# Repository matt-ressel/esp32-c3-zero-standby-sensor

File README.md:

# ESP32-C3 Zero-Standby Environmental Sensor

## 🎯 Project Goal

To create a wireless, battery-powered environmental sensor, optimized for extremely low power consumption. The primary goal is to achieve a theoretical battery life exceeding **10 years** on a single Li-SOCl₂ (e.g., FANSO ER18505M 3.6V, 3500mAh) battery.

This project achieves this goal through a unique **"Zero Standby"** architecture, where the microcontroller is completely disconnected from power during its idle state. The duty cycle is managed by an external, nano-power system timer.

---

## 🚀 Key Features & Architecture

*   **Ultra-Low Electronic Quiescent Current:** The total current consumed by the electronics in the power-off state has been meticulously optimized to be under 100 nA. This value is the sum of the quiescent currents (Iq) of all components permanently connected to the battery:
    *   **TPS63900 Buck-Boost (in shutdown):** ~60 nA
    *   **TPL5111 System Timer:** ~35 nA
    *   **SiP32431 Load Switch (in off-state):** ~0.01 nA (practically zero)
    *   **Total Electronic Iq ≈ 95 nA**

    This successfully achieves the design goal of making the electronic footprint in the standby state almost immeasurable. It ensures that the theoretical battery life is maximized, being limited almost exclusively by the energy consumed during the brief active cycles.
*   **Power Gating Architecture:** Instead of using Deep Sleep mode, the TPL5111 completely enables and disables the power supply for the entire system (MCU + sensor), eliminating any MCU-related leakage currents.
*   **Ultra-Fast On-Time:** The entire active cycle (boot, measure, transmit, shutdown) is highly optimized to complete in **well under 100 milliseconds** (typically ~80ms), which is critical for minimizing energy consumption.
*   **Optimized Operational Sequence:** The firmware uses advanced techniques like **latency hiding**, where long physical processes (like battery measurement stabilization) are executed in the background during other necessary initializations (like the Wi-Fi stack), effectively reducing their time cost to zero.
*   **ESP-NOW Communication:** Utilizes the lightweight and fast ESP-NOW protocol, configured for Long Range (LR) mode, for robust and low-power data transmission.
*   **Professional Component-Based Architecture:** The code is structured into fully independent, reusable components (e.g., `bme280_driver`, `espnow_sender`, `sensor_manager`) in line with the best practices for ESP-IDF, ensuring clean separation of concerns and easy maintenance.

---

## 🛠️ Hardware Components (Bill of Materials)

| Component             | Model/Value                                     | Role                                                     |
| --------------------- | ----------------------------------------------- | -------------------------------------------------------- |
| **Microcontroller**   | Espressif ESP32-C3-MINI-1                       | Main processing unit, RF communication                   |
| **System Timer**        | Texas Instruments TPL5111                       | External watchdog and duty cycle manager (Power Gating)  |
| **Buck-Boost Converter**| Texas Instruments TPS63900                      | High-efficiency 3.3V voltage regulation                |
| **Environmental Sensor**| Bosch BME280                                    | Measures temperature, humidity, and pressure (I²C)       |
| **Battery**             | FANSO ER18505M (Li-SOCl₂, 3.6V, 3500mAh) or similar | Primary power source                                     |
| **Load Switch**         | Vishay SiP32431                                 | Switched voltage divider for V_BATT measurement        |

---

## 🔄 Optimized Software Operational Sequence

The duty cycle is fast, repeatable, and designed for maximum efficiency. The order of operations is critical.

1.  **START (Cold Boot):** The TPL5111 activates the power converter, supplying power to the system. `app_main` begins execution.

2.  **IMMEDIATE CRITICAL ACTIONS:**
    *   **Initialize Critical Drivers:** The bare minimum of drivers needed for immediate measurements are initialized (`bme280_driver`, `battery_monitor`, `power_manager`).
    *   **Start Battery Measurement:** The firmware immediately enables the external voltage divider. This starts the ~25ms physical process of charging the filter capacitor. This process now runs **in the background**.
    *   **Perform BME280 Measurement:** With the battery measurement stabilizing in the background, the CPU **immediately** performs the BME280 sensor reading. This is done as early as possible to get a temperature reading before the CPU core begins to self-heat.

3.  **LATENCY HIDING & NETWORK INIT:**
    *   While the battery measurement capacitor is charging, the firmware productively uses this time to initialize the time-consuming network stack (`wifi_service` and `espnow_sender`). This **hides the 25ms delay**, effectively making the battery stabilization time "free".

4.  **FINALIZE & TRANSMIT:**
    *   Control is passed to the `sensor_manager`.
    *   It **finalizes the battery measurement** by reading the now-stable voltage from the ADC.
    *   It assembles all data (BME280, battery) into a payload, calculates a CRC, and hands it to the `espnow_sender`.
    *   The `espnow_sender` transmits the packet and waits for a hardware-level acknowledgement (ACK) from the receiver.

5.  **SHUTDOWN:**
    *   Upon completion of the transmission (successful or not), a HIGH pulse is generated on the `DONE` pin.
    *   The TPL5111 receives the signal and immediately cuts off power to the system.
    *   A **fail-safe mechanism** is in place: if the shutdown signal fails, the MCU enters its deepest possible sleep state to conserve energy until the TPL5111's own watchdog timer performs a hard power cycle.

---

## ⚙️ Getting Started & Configuration

This project is designed for rapid setup using the provided configuration files, while still requiring user-specific network details.

### 1. Mandatory User Configuration (menuconfig)

This repository includes a pre-configured `sdkconfig` file containing all the performance optimizations listed below. This saves you the time of setting them manually.

**However, you MUST configure your own network-specific parameters before building and flashing.**

To do this, run `idf.py menuconfig` and navigate to the following menu:

`---> ESP32C3 Zero Standby Sensor Configuration`

Inside this menu, you must set the following values to match your receiver/gateway:

*   **`Gateway MAC Address`**: The MAC address of your ESP-NOW receiver.
*   **`ESPNOW primary master key (PMK)`**: A 16-character string shared with the receiver.
*   **`ESPNOW local master key (LMK)`**: A 16-character string shared with the receiver for this specific device.
*   **`ESPNOW Channel`**: The Wi-Fi channel (1-13) on which both devices will communicate.
*   **`I2C Pin Configuration`**: Specify the GPIO pins used by the I2C master for the BME280.

### 2. Summary of Key Performance Optimizations

For reference, here is a detailed list of the critical optimizations applied in the provided `sdkconfig` to achieve an ultra-fast boot time (cold boot to shutdown in < 100ms).

The following options, configured via `idf.py menuconfig`, are essential for minimizing boot time and runtime power consumption.

#### Compiler Optimization
For maximum performance, both the main application and the bootloader should be compiled with `-O2` optimization.
*   **Application Optimization Level:**
    *   `Compiler options ---> Optimization Level ---> Optimize for performance (-O2)`

*   **Bootloader Optimization Level:**
    *   `Bootloader config ---> Bootloader optimization level ---> Optimize for performance (-O2)`

#### Bootloader & Logging & System
*   **Disable Console Output (CRITICAL):** Disables the UART console driver entirely. This removes the initialization overhead of the UART peripheral and converts all logging macros to no-ops, significantly speeding up boot and execution.
    *   `Component config ---> ESP System Settings ---> Channel for console output (None)`

*   **Skip Image Validation:** This is a major optimization. It instructs the bootloader to skip the time-consuming SHA-256 validation of the application image on every boot.
    *   `Bootloader config ---> [*] Skip image validation always`

*   **Disable Bootloader Log:** Drastically speeds up the initial boot phase.
    *   `Bootloader config ---> Log ---> Bootloader log verbosity ---> No output`

*   **Disable Application Log:** Frees up CPU cycles and reduces on-time. Set to "Info" for debugging and "None" for production.
    *   `Component config ---> Log ---> Log Level ---> Default log verbosity ---> No output`

*   **FreeRTOS:** The project is configured for a single core and a 1000Hz tick rate.
    *   `Component config ---> FreeRTOS ---> Kernel ---> configTICK_RATE_HZ (1000)`

#### ADC & RTC Optimizations
*   **Place ADC ISR in IRAM:** Improves performance of ADC reads by running the code from faster RAM instead of flash.
    *   `Component config ---> ADC ---> [*] Place ISR version ADC oneshot mode read function into IRAM`

*   **Skip RTC Clock Calibration:** Reduces boot time by skipping a time-consuming calibration step.
    *   `Component config ---> Hardware Settings ---> RTC Clock Config ---> (0) Number of cycles for RTC_SLOW_CLK calibration`    

#### Wi-Fi, PHY & LWIP Stack Reduction
The goal is to strip down the network stack to the bare minimum required for ESP-NOW.
*   **Reduce Max TX Power:** A critical setting to reduce peak current draw and stay within the limits of the power supply and battery. 18dBm is a safe starting point.
    *   `Component config ---> Wi-Fi ---> (18) Max WiFi TX power (dBm)`
    
*   **Enable Brownout Power Reduction:** A fail-safe mechanism that reduces Tx power on the next boot if a brownout occurs.
    *   `Component config ---> PHY ---> [*] Reduce PHY TX power when brownout reset`

*   **Disable Unused Wi-Fi Features:** ESP-NOW does not require SoftAP, WPA3, Enterprise security, or OWE. Disabling these significantly reduces the final binary size and memory footprint.
    *   `Component config ---> Wi-Fi ---> [ ] WiFi SoftAP Support`
    *   `Component config ---> Wi-Fi ---> Security features ---> [ ] Enable WPA3-Personal`
    *   And other similar options...

*   **Disable LWIP (TCP/IP Stack):** ESP-NOW operates at the MAC layer and does not use the TCP/IP stack (LWIP). Disabling IPv6 and DHCP server further reduces code size and memory usage.
    *   `Component config ---> LWIP ---> [ ] Enable IPv6`
    *   `Component config ---> LWIP ---> [ ] DHCPS: Enable IPv4 Dynamic Host Configuration Protocol Server (DHCPS)`

#### Flash & PHY
*   **SPI Flash Configuration:** Using the fastest possible mode and frequency reduces the time spent loading the application from flash.
    *   `Serial flasher config ---> Flash SPI mode ---> QIO`
    *   `Serial flasher config ---> Flash SPI speed ---> 80 MHz`
    
*   **Disable PHY Calibration:** Skips Wi-Fi/Bluetooth PHY calibration on boot, saving a significant amount of time. This is safe as calibration data is stored in NVS and loaded on first boot.
    *   `Component config ---> PHY ---> [*] Store phy calibration data in NVS`
    *   `Component config ---> PHY ---> Calibration mode (Calibration none)`
 
### 3. Boot ROM Log Disable (eFuse) - CRITICAL STEP

By default, the ESP32-C3's internal Boot ROM prints diagnostic messages to the UART during the very first moments of startup. This adds a significant delay. Disabling this is a **one-way, irreversible operation** that requires burning eFuses.

**Warning: Burning eFuses is permanent. Proceed with caution.**

To achieve the fastest possible boot time, connect the device and run the following commands using `espefuse.py`:

```bash
# Disable ROM logs for UART0
espefuse.py --port YOUR_PORT burn_efuse UART_PRINT_CONTROL 3

# For ESP32-C3 with built-in USB-JTAG, also disable its ROM logs
espefuse.py --port YOUR_PORT burn_efuse DIS_USB_SERIAL_JTAG_ROM_PRINT 1    

```

## 📉 Real-World Performance Verification

The theoretical optimizations have been verified using a **Nordic Power Profiler Kit II (PPK2)**. The chart below captures a single, complete active cycle — from cold boot, through sensor reading and Wi-Fi initialization, to ESP-NOW transmission and final power-off.

*(Fig. 1: Complete active cycle profile captured with PPK2 @ 3.6V)*

### Measured Metrics (per cycle):

| Metric | Measured Value | Significance |
| :--- | :--- | :--- |
| **Total On-Time** | **~80 ms** | Surpasses the goal of < 100ms. Minimizes the time the battery is under load. |
| **Total Charge** | **~3.05 mC** | Extremely low energy cost per transmission. **1 mC ≈ 0.278 µAh**, so one cycle costs just **~0.85 µAh**. |
| **Average Current** | **~38 mA** | Efficient operation during the active phase. |
| **Peak Current** | **~430 mA** | Represents the short Wi-Fi TX burst. Handled by input capacitors to protect the high-impedance battery. |

**Conclusion:** With a total charge of **3.05 mC** per cycle and a 10-minute interval, the average current consumption of the electronics is approximately **0.25 µA** (plus the ~200nA quiescent current). This confirms that the system's battery life is strictly limited by the battery's self-discharge rate, not the device's power consumption.

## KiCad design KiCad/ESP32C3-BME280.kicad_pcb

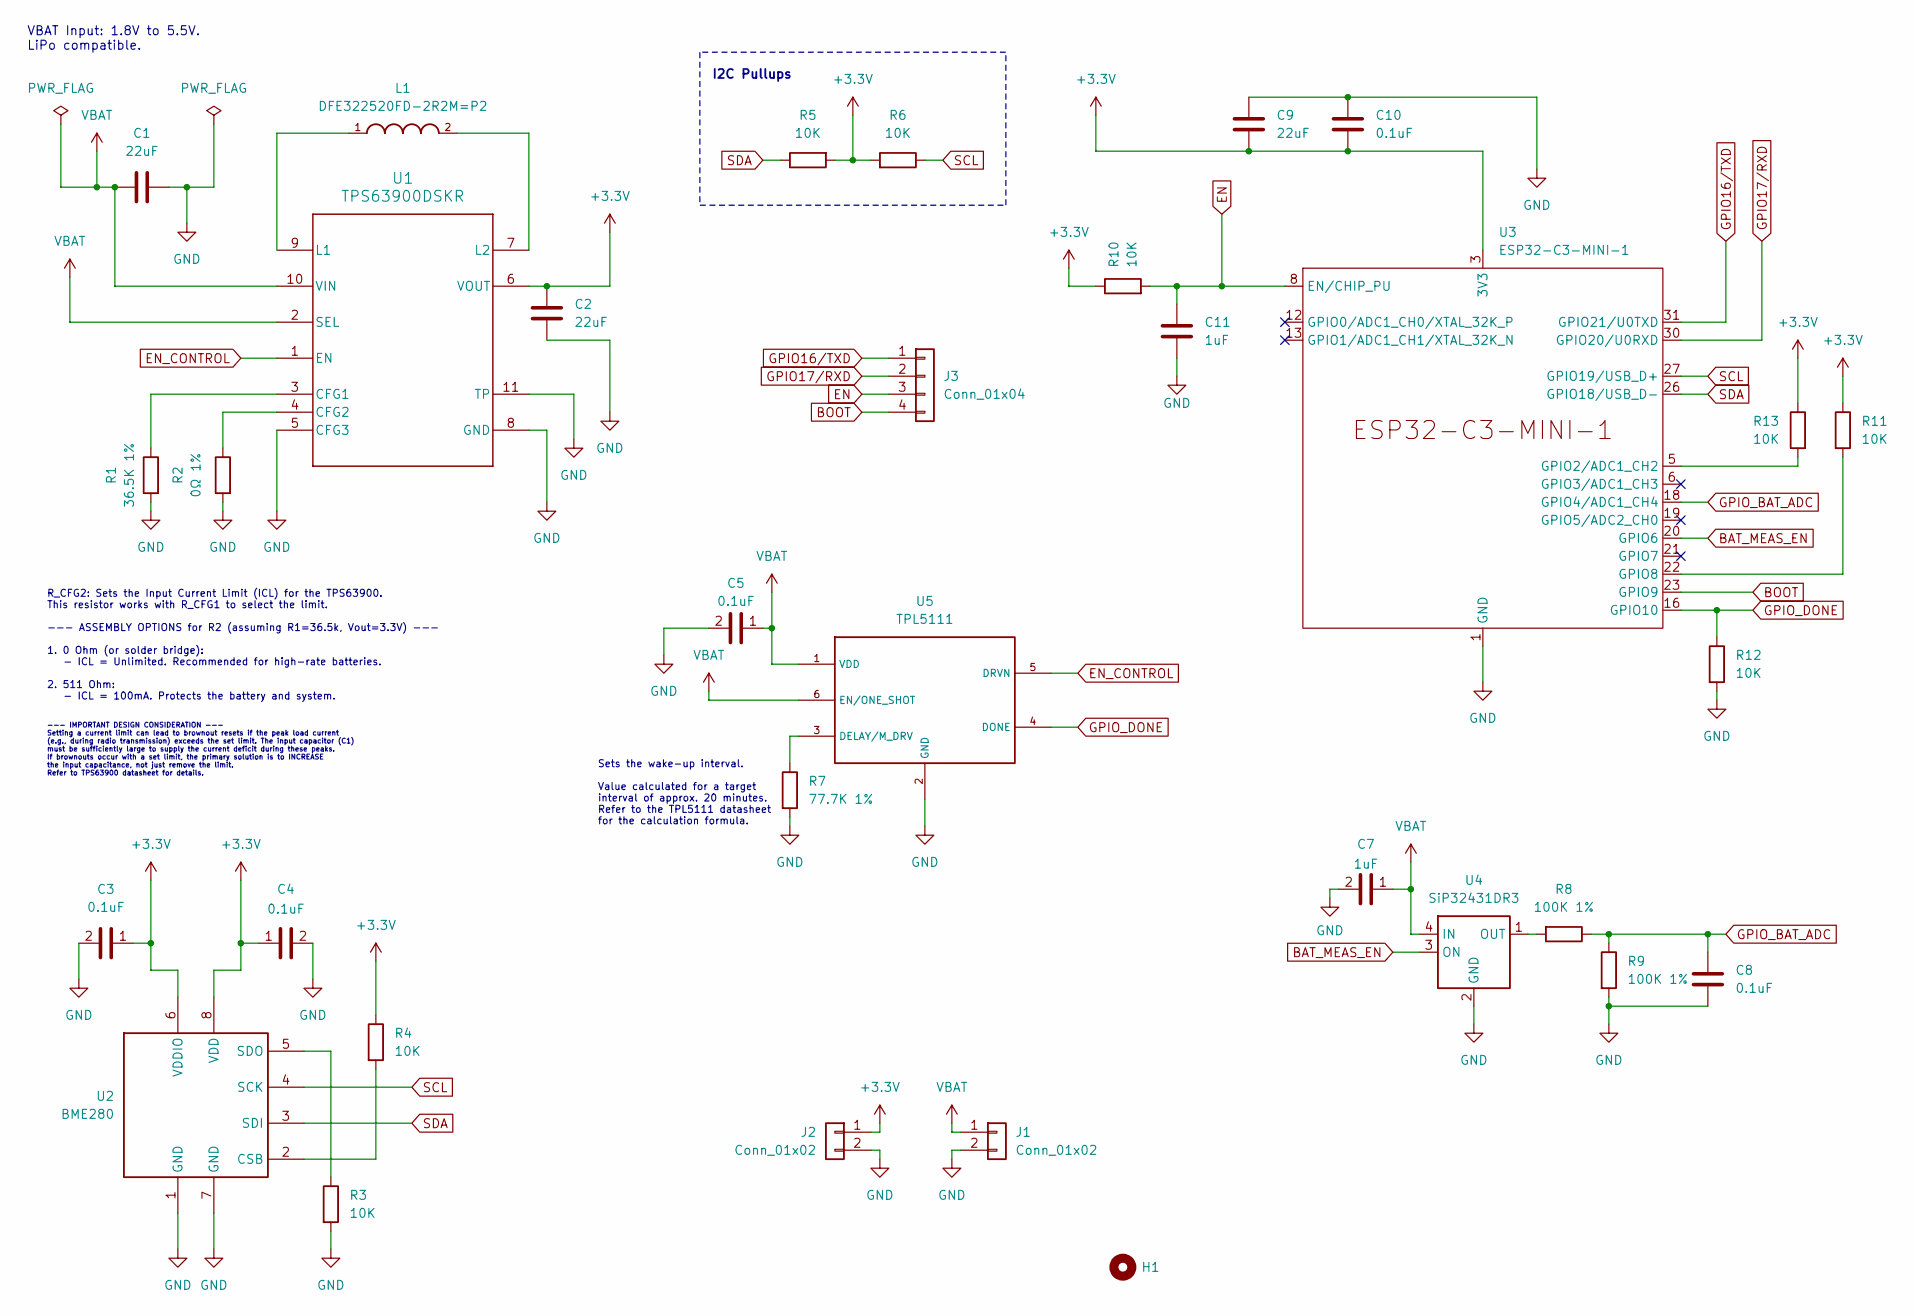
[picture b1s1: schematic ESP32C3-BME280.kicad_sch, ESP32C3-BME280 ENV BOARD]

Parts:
C1, C2, C9: 22uF; C_0805_2012Metric
C3, C4, C5, C8, C10: 0.1uF; C_0603_1608Metric
C7, C11: 1uF; C_0603_1608Metric
H1: MountingHole; MountingHole_2.2mm_M2_ISO7380_Pad
J1, J2: Conn_01x02; PinHeader_1x02_P2.00mm_Vertical
J3: Conn_01x04; PinHeader_1x04_P2.00mm_Vertical
L1: DFE322520FD-2R2M=P2; INDC3225X200N
R1: 36.5K 1%; R_0603_1608Metric
R2: 0Ω 1%; R_0603_1608Metric
R3, R4, R5, R6, R10, R11, R12, R13: 10K; R_0603_1608Metric
R7: 77.7K 1%; R_0603_1608Metric
R8, R9: 100K 1%; R_0603_1608Metric
U1: TPS63900DSKR; DSK0010A
U2: BME280; Bosch_LGA-8_2.5x2.5mm_P0.65mm_ClockwisePinNumbering
U3: ESP32-C3-MINI-1
U4: SiP32431DR3; SOT-363_SC-70-6
U5: TPL5111; SOT-23-6

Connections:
+3.3V: C2.1, C3.1, C4.1, C9.1, C10.1, J2.1, R4.1, R5.2, R6.2, R10.1, R11.1, R13.1, U1.6 (VOUT), U2.6 (VDDIO), U2.8 (VDD), U3.3 (3V3)
BAT_MEAS_EN: U3.20 (GPIO6), U4.3 (ON)
BOOT: J3.4, U3.23 (GPIO9)
EN: C11.1, J3.3, R10.2, U3.8 (EN/CHIP_PU)
EN_CONTROL: U1.1 (EN), U5.5 (DRVN)
GND: C1.2, C2.2, C3.2, C4.2, C5.2, C7.2, C8.2, C9.2, C10.2, C11.2, J1.2, J2.2, R1.2, R2.2, R3.2, R7.2, R9.2, R12.2, U1.5 (CFG3), U1.8 (GND), U1.11 (TP), U2.1 (GND), U2.7 (GND), U3.1 (GND), U3.2 (GND), U3.11 (GND), U3.14 (GND), U3.36 (GND), U3.37 (GND), U3.38 (GND), U3.39 (GND), U3.40 (GND), U3.41 (GND), U3.42 (GND), U3.43 (GND), U3.44 (GND), U3.45 (GND), U3.46 (GND), U3.47 (GND), U3.48 (GND), U3.49 (GND), U3.50 (GND), U3.51 (GND), U3.52 (GND), U3.53 (GND), U4.2 (GND), U4.5 (GND), U5.2 (GND)
GPIO16/TXD: J3.1, U3.31 (GPIO21/U0TXD)
GPIO17/RXD: J3.2, U3.30 (GPIO20/U0RXD)
GPIO_BAT_ADC: C8.1, R8.1, R9.1, U3.18 (GPIO4/ADC1_CH4)
GPIO_DONE: R12.1, U3.16 (GPIO10), U5.4 (DONE)
unnamed: R1.1, U1.3 (CFG1)
unnamed: R2.1, U1.4 (CFG2)
unnamed: L1.1, U1.9 (L1)
unnamed: L1.2, U1.7 (L2)
unnamed: R4.2, U2.2 (CSB)
unnamed: R3.1, U2.5 (SDO)
unnamed: R13.2, U3.5 (GPIO2/ADC1_CH2)
unnamed: R11.2, U3.22 (GPIO8)
unnamed: R8.2, U4.1 (OUT)
unnamed: R7.1, U5.3 (DELAY/M_DRV)
SCL: R6.1, U2.4 (SCK), U3.27 (GPIO19/USB_D+)
SDA: R5.1, U2.3 (SDI), U3.26 (GPIO18/USB_D-)
VBAT: C1.1, C5.1, C7.1, J1.1, U1.2 (SEL), U1.10 (VIN), U4.4 (IN), U5.1 (VDD), U5.6 (EN/ONE_SHOT)

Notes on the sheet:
Sets the wake-up interval. Value calculated for a target interval of approx. 20 minutes. Refer to the TPL5111 datasheet for the calculation formula.
R_CFG2: Sets the Input Current Limit (ICL) for the TPS63900. This resistor works with R_CFG1 to select the limit. --- ASSEMBLY OPTIONS for R2 (assuming R1=36.5k, Vout=3.3V) --- 1. 0 Ohm (or solder bridge): - ICL = Unlimited. Recommended for high-rate batteries. 2. 511 Ohm: - ICL = 100mA. Protects t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
I2C Pullups
--- IMPORTANT DESIGN CONSIDERATION --- Setting a current limit can lead to brownout resets if the peak load current (e.g., during radio transmission) exceeds the set limit. The input capacitor (C1) must be sufficiently large to supply the current deficit during these peaks. If brownouts occur with 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
VBAT Input: 1.8V to 5.5V. LiPo compatible.

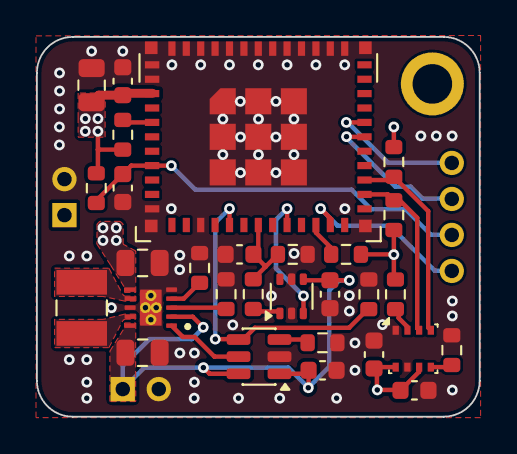
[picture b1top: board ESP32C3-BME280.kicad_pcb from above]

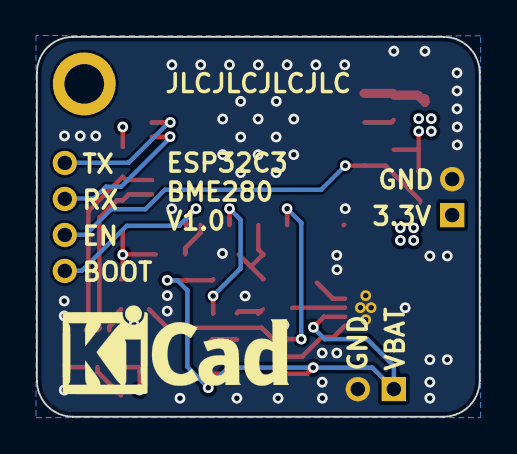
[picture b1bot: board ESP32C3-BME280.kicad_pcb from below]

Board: 4 copper layers, 24.6 x 21.1 mm, 33 parts (3 on the bottom side), 23 nets.

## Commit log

2025-10-12 Initial
2025-10-12 Add KiCad files
2025-10-12 Remove
2025-10-12 Add sdkconfig to .gitignore
2025-10-12 Refactor Kconfig.projbuild: Remove WiFi configuration options and add Gateway MAC address
2025-10-12 Enhance CMakeLists.txt: Add support for processing gateway MAC address from Kconfig
2025-10-12 Refactor main.c: Enhance documentation and structure of app_main function
2025-10-12 Add ESP-NOW transmitter and WiFi initialization modules with detailed documentation
2025-10-20 Add CRC-8 checksum implementation: Introduce crc8.c and crc8.h for CRC-8 calculation with detailed documentation
2025-10-20 Add I2C configuration options: Introduce I2C SDA pin, SCL pin, and master frequency settings in Kconfig.projbuild
2025-10-20 Set idf build property: "MINIMAL_BUILD ON"
2025-10-20 Add shared component CMakeLists.txt and sensor_data.h: Define structure for sensor readings with detailed documentation
2025-10-20 Add BME280 driver implementation: Introduce bme280_driver.c and bme280_driver.h for sensor communication and data handling
2025-10-20 Add ESP-NOW sender module: Implement espnow_sender.c and espnow_sender.h for ESP-NOW initialization, data transmission, and status handling
2025-10-20 Fix author formatting in ESP-NOW sender module documentation
2025-10-20 Refactor logging tag comment in BME280 driver for clarity
2025-10-20 Add sensor manager component: Implement sensor_manager.c and sensor_manager.h for data acquisition, processing, and transmission
2025-10-20 Add WiFi service component: Implement wifi_service.c and wifi_service.h for WiFi initialization and ESP-NOW configuration
2025-10-20 Add CMakeLists.txt for utils component: Register utility functions including CRC calculations
2025-10-20 Remove WiFi initialization module: Delete wifi.c and wifi.h files as part of refactoring
2025-10-23 Delete
2025-10-28 Update README.md: Enhance project goal and key features descriptions for clarity and detail
2025-10-28 Add Battery Monitor and Power Manager components: Implement CMakeLists.txt, source, and header files for battery monitoring and power management functionalities
2025-10-28 Refactor CMakeLists.txt: Remove unused MAC address processing code and streamline component registration
2025-10-28 Refactor main.c: Enhance documentation, optimize initialization phases, and improve logging for sensor lifecycle management
2025-11-16 Add battery monitor component: Implement source and header files for battery voltage measurement, including initialization, measurement, and de-initialization functions.
2025-11-16 Add Power Manager component: Implement source and header files for power management, including initialization, de-initialization, and shutdown functionalities.
2025-11-16 Update BME280 driver: Increment version to 0.2, enhance initialization checks, and improve logging for data readings
2025-11-16 Update ESP-NOW sender module: Increment version to 0.2, add initialization flag, and enhance error handling for transmission operations.
2025-11-16 Update sensor manager: Increment version to 0.2, enhance BME280 data processing, and improve battery measurement handling.
2025-11-16 Update main application: Increment version to 1.0, refactor initialization error handling, and improve logging for BME280 measurements.
2025-12-01 Fix logging statement in app_main to ensure proper initialization message is logged
2025-12-20 Update README.md: Clarify electronic quiescent current terminology and enhance project setup instructions
2025-12-20 Add sdkconfig file
2025-12-20 Remove redundant explanation for ESPNOW local master key in Kconfig.projbuild
2026-01-01 Update BME280 driver: Correct pressure value comment to reflect Q24.8 format
2026-01-01 Refactor wifi_service.c: Comment out unused MAC address retrieval and logging statements
2026-01-01 Update README.md: Enhance ultra-fast on-time description and add real-world performance verification section
2026-01-01 Fix temperature calculation in sensor_manager_run function
2026-01-01 Add PPK2 cycle profile image for reference in documentation
2026-01-01 Update sdkconfig: Disable default console UART and set UART parameters to -1
